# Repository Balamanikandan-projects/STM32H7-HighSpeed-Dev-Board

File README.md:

# STM32H7-HighSpeed-Dev-Board
An interview-ready, high-performance development platform designed around the ARM Cortex-M7 **STM32H743VIT6** microcontroller (operating at up to 480 MHz). This project showcases advanced hardware engineering principles, including 4-layer PCB stackup optimization, high-speed digital signal integrity, and isolated power management switching nodes.

## 🚀 Key Features & Specifications
* **Core Processor:** STM32H743VIT6 (ARM Cortex-M7, 480 MHz, 100-pin LQFP package).
* **Power Management:** On-board **TLV62569** high-efficiency synchronous DC-DC buck regulator stepping down 5V USB power to a stable 3.3V system rail.
* **Storage Interface:** MicroSD Card slot supporting high-bandwidth SDMMC communication profiles.
* **Connectivity:** Integrated USB-C interface protected by a **USBLC6-2SC6** low-capacitance ESD protection array.
* **Clock Systems:** Dual external oscillators—a high-speed 25 MHz system clock and a low-speed 32.768 kHz RTC clock with optimized parallel trace routing.

---

## 🛠️ Hardware Architecture & Schematic Layout

The schematic is organized into strict, modular functional blocks to ensure clean system readability:
1. **Power Supply & Input:** Raw 5V input via USB-C routed directly through ESD clamping protection into the synchronous buck regulator loop.
2. **Core Processor:** Centralized STM32H7 MCU hub surrounded closely by dedicated decoupling capacitor networks.
3. **Peripheral Storage:** High-speed data links mapped to the MicroSD interface.

---

## 🏎️ PCB Design & Signal Integrity (SI) Strategy

Designing for a 480 MHz processor requires moving beyond standard 2-layer routing limitations. This board utilizes a professional **4-layer stackup** optimized for electromagnetic compatibility (EMC):

### 🥞 4-Layer Stackup Assignment
* **Layer 1 (Top):** Component placement and high-speed signal routing.
* **Layer 2 (Inner 1):** Solid, unbroken **GND Reference Plane**.
* **Layer 3 (Inner 2):** Power Plane split into 5V and 3.3V distribution zones.
* **Layer 4 (Bottom):** Slower control lines and trace cleanup.

### 📐 Engineering Layout Constraints Implemented
* **Minimized Return Path Loops:** Every single ground pad drops directly into the Layer 2 GND plane using an adjacent via, dropping loop inductance to near-zero and eliminating ground bounce.
* **High-Speed Clock Routing:** The 25 MHz oscillator lines are short, perfectly symmetric, and run completely parallel to eliminate phase jitter.
* **EMI Suppression:** The switching node of the TLV62569 buck regulator (including input/output caps and the 1.5µH inductor) is laid out in a tight, isolated geometric loop to compress high-frequency switching noise away from analog rails.

---

## 📦 Manufacturing & Assembly Ready

The project contains a complete, automated manufacturing release package generated directly from KiCad:
* **Gerber Blueprints:** Complete 4-layer physical production layers.
* **Excellon Drill Files:** Accurate CNC hole dimensions for vias and mounting pins.
* **Bill of Materials (BOM):** Fully specified manufacturing part numbers.
* **Component Placement Files (CPL):** Pick-and-place centroid data ($X,Y$ coordinates and rotation angles) for automated assembly.

### 🔍 3D Board Visualization

---

## 📂 How to Open This Project
1. Clone this repository.
2. Download and install **KiCad v7 or later**.
3. Open the `.kicad_pro` project file to explore the fully cleared DRC schema and layout!

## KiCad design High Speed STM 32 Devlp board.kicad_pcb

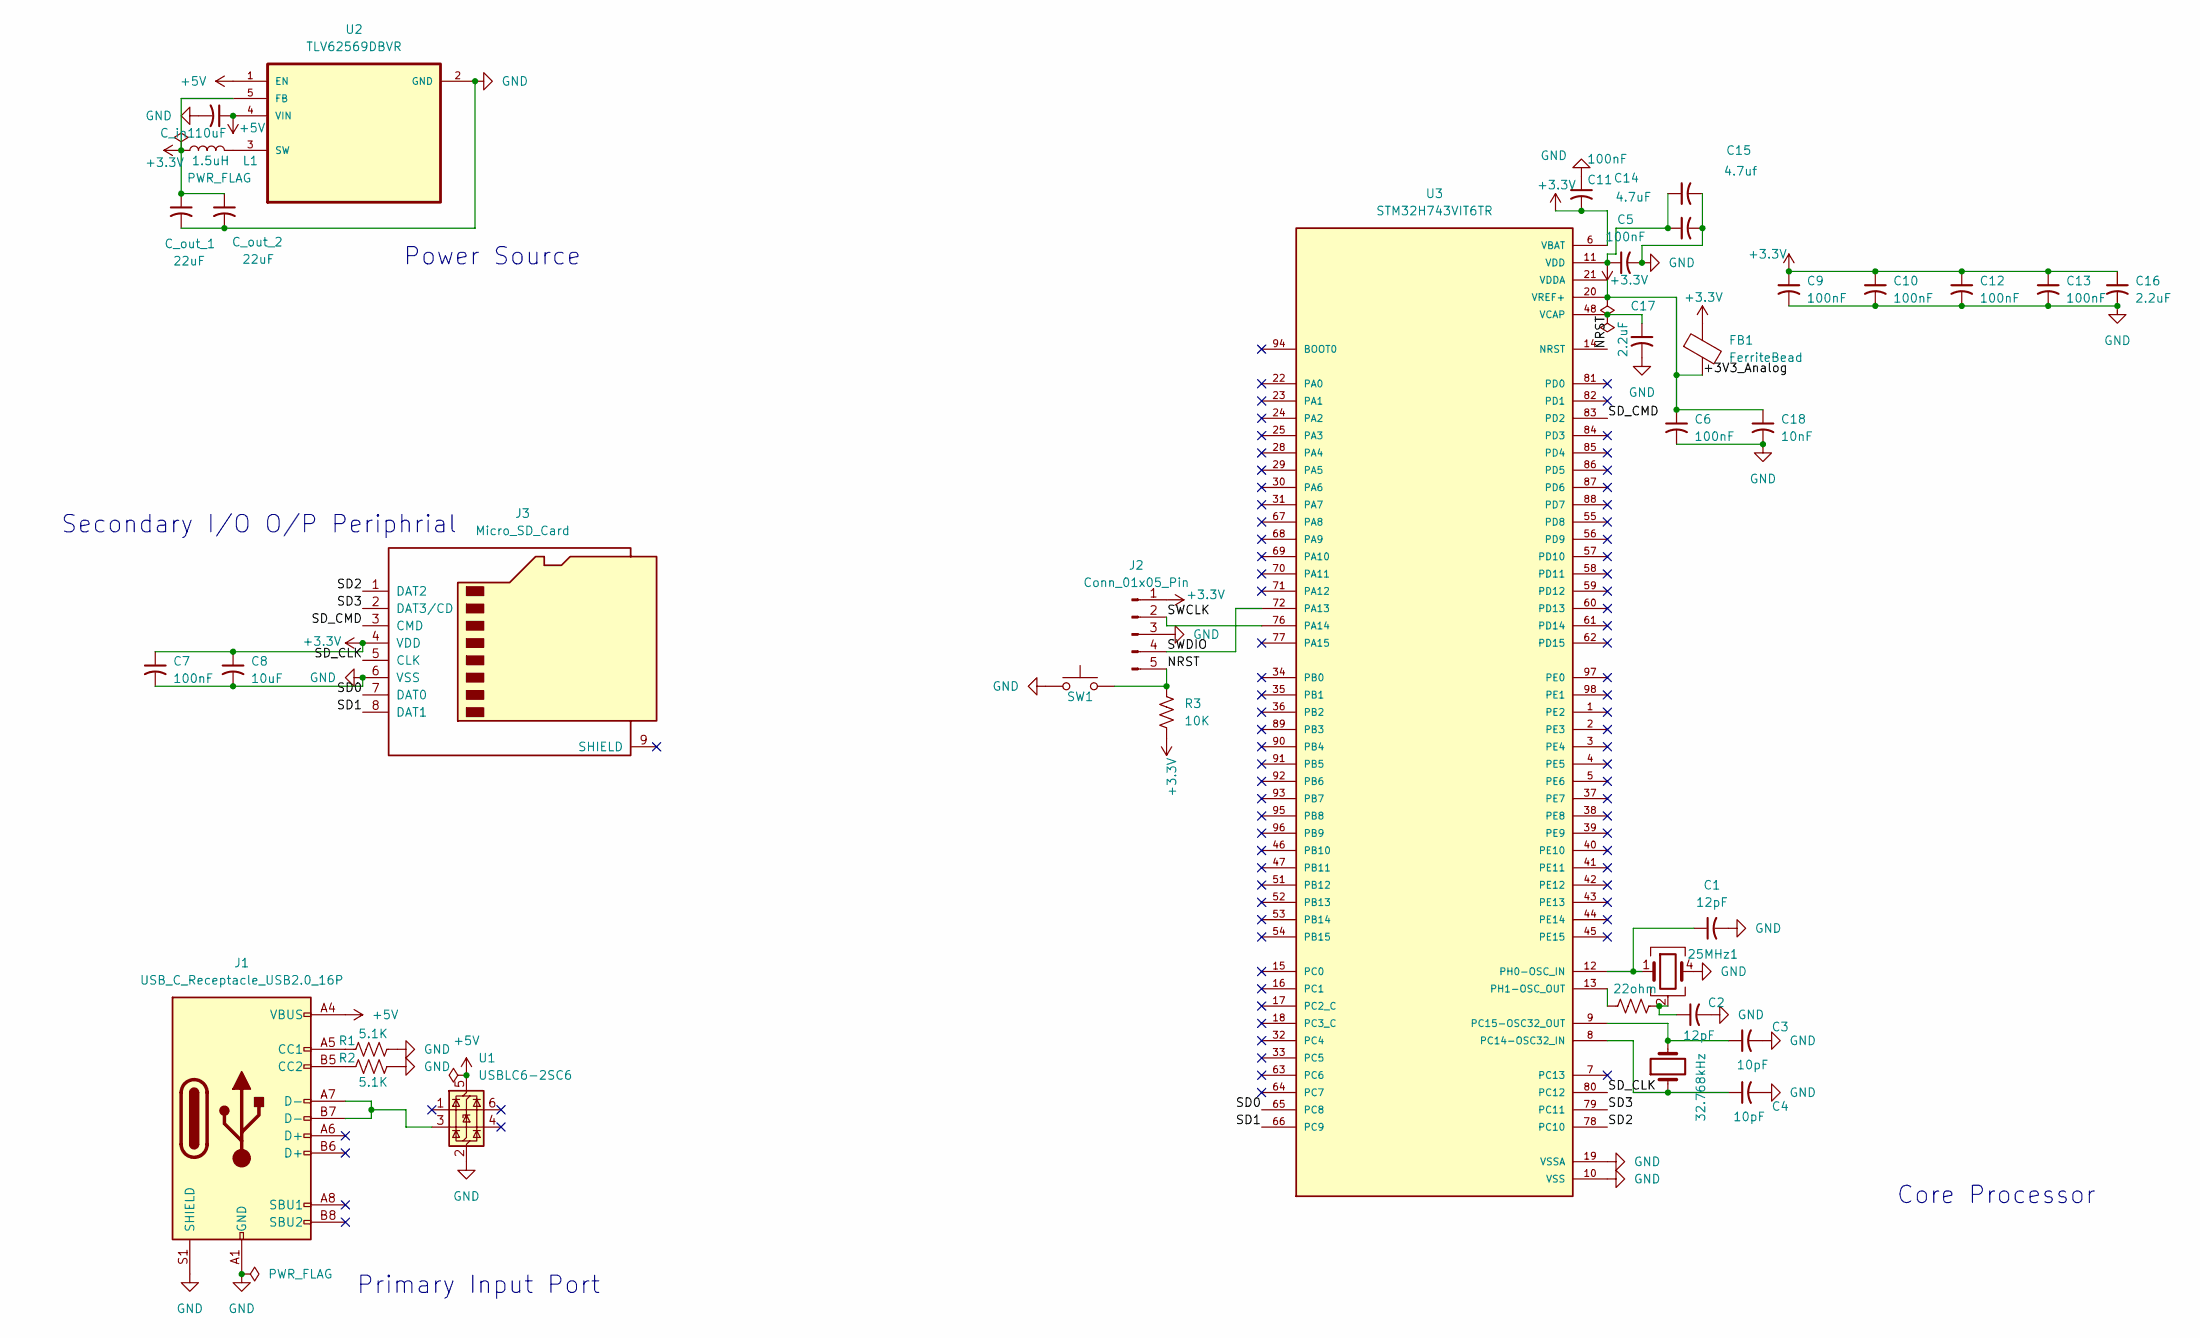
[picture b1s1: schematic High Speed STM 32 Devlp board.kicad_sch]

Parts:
25MHz1: Crystal_GND23; Crystal_SMD_3225-4Pin_3.2x2.5mm
C1, C2: 12pF; C_0603_1608Metric
C3, C4: 10pF; C_0603_1608Metric
C5, C6, C7, C9, C10, C11, C12, C13: 100nF; C_0603_1608Metric
C8: 10uF; C_0603_1608Metric
C14: 4.7uF; C_0603_1608Metric
C15: 4.7uf; C_0603_1608Metric
C16, C17: 2.2uF; C_0603_1608Metric
C18: 10nF; C_0603_1608Metric
C_in1: 10uF; C_0603_1608Metric
C_out_1, C_out_2: 22uF; C_0603_1608Metric
FB1: FerriteBead; R_0603_1608Metric
J1: USB_C_Receptacle_USB2.0_16P; USB_C_Receptacle_GCT_USB4085
J2: Conn_01x05_Pin; PinHeader_1x05_P2.54mm_Vertical
J3: Micro_SD_Card; microSD_HC_Molex_47219-2001
L1: 1.5uH; L_Wuerth_MAPI-3012
R1, R2: 5.1K; R_0603_1608Metric
R3: 10K; R_0603_1608Metric
R_Damp1: 22ohm; R_0603_1608Metric
SW1: SW_MEC_5G; SW_MEC_5GSH9
U1: USBLC6-2SC6; SOT-23-6
U2: TLV62569DBVR; SOT-23-5; DigiKey_Part_Number 296-47360-1-ND
U3: STM32H743VIT6TR; LQFP-100-1EP_14x14mm_P0.5mm_EP6.9x6.9mm; PARTREV 7; DigiKey_Part_Number 497-STM32H743VIT6TRCT-ND
Y1: 32.768kHz; Crystal_SMD_3215-2Pin_3.2x1.5mm

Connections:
+3.3V: C5.1, C7.1, C8.1, C9.1, C10.1, C11.2, C12.1, C13.1, C14.1, C15.1, C16.1, C_out_1.1, C_out_2.1, FB1.1, J2.1, J3.4 (VDD), L1.1, R3.1, U2.5 (FB), U3.6 (VBAT), U3.11 (VDD), U3.27 (VDD), U3.50 (VDD), U3.75 (VDD), U3.100 (VDD)
+5V: C_in1.1, J1.A4 (VBUS), J1.A9 (VBUS), J1.B4 (VBUS), J1.B9 (VBUS), U1.5 (VBUS), U2.1 (EN), U2.4 (VIN)
/+3V3_Analog: C6.1, C18.1, FB1.2, U3.20 (VREF+), U3.21 (VDDA)
/NRST: J2.5, R3.2, SW1.3 (B), SW1.4 (B), U3.14 (NRST)
/SD0: J3.7 (DAT0), U3.65 (PC8)
/SD1: J3.8 (DAT1), U3.66 (PC9)
/SD2: J3.1 (DAT2), U3.78 (PC10)
/SD3: J3.2 (DAT3/CD), U3.79 (PC11)
/SD_CLK: J3.5 (CLK), U3.80 (PC12)
/SD_CMD: J3.3 (CMD), U3.83 (PD2)
/SWCLK: J2.2, U3.76 (PA14)
/SWDIO: J2.4, U3.72 (PA13)
GND: 25MHz1.4, C1.2, C2.2, C3.2, C4.2, C5.2, C6.2, C7.2, C8.2, C9.2, C10.2, C11.1, C12.2, C13.2, C14.2, C15.2, C16.2, C17.2, C18.2, C_in1.2, C_out_1.2, C_out_2.2, J1.A1 (GND), J1.A12 (GND), J1.B1 (GND), J1.B12 (GND), J1.S1 (SHIELD), J2.3, J3.6 (VSS), R1.2, R2.2, SW1.1 (A), SW1.2 (A), U1.2 (GND), U2.2 (GND), U3.10 (VSS), U3.19 (VSSA), U3.26 (VSS), U3.49 (VSS), U3.74 (VSS), U3.99 (VSS)
unnamed: 25MHz1.2 (G), 25MHz1.3 (G), C2.1, R_Damp1.2
unnamed: J1.A5 (CC1), R1.1
unnamed: J1.B5 (CC2), R2.1
unnamed: J1.A7 (D-), J1.B7 (D-), U1.3 (I/O2)
unnamed: L1.2, U2.3 (SW)
unnamed: C4.1, U3.8 (PC14-OSC32_IN), Y1.1
unnamed: C3.1, U3.9 (PC15-OSC32_OUT), Y1.2
unnamed: 25MHz1.1, C1.1, U3.12 (PH0-OSC_IN)
unnamed: R_Damp1.1, U3.13 (PH1-OSC_OUT)
VCAP: C17.1, U3.48 (VCAP), U3.73 (VCAP)

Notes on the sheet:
Secondary I/O O/P Periphrial
Primary Input Port
Core Processor
Power Source

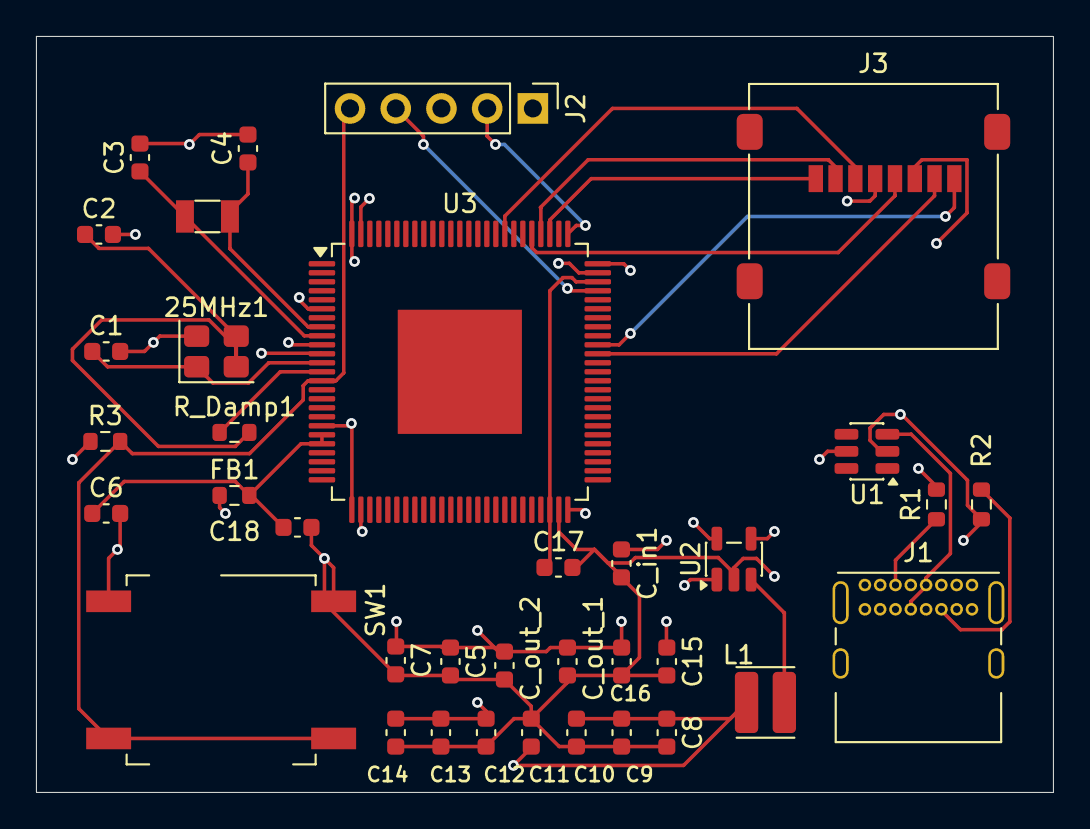
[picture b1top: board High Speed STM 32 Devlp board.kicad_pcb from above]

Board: 4 copper layers, 56.5 x 42.0 mm, 36 parts (0 on the bottom side), 23 nets.

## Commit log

2026-06-09 README.md
2026-06-09 Add files via upload
    Add fabrication-ready project design and manufacturing files
2026-06-09 Update README.md
    Add fabrication-ready project design and manufacturing files
